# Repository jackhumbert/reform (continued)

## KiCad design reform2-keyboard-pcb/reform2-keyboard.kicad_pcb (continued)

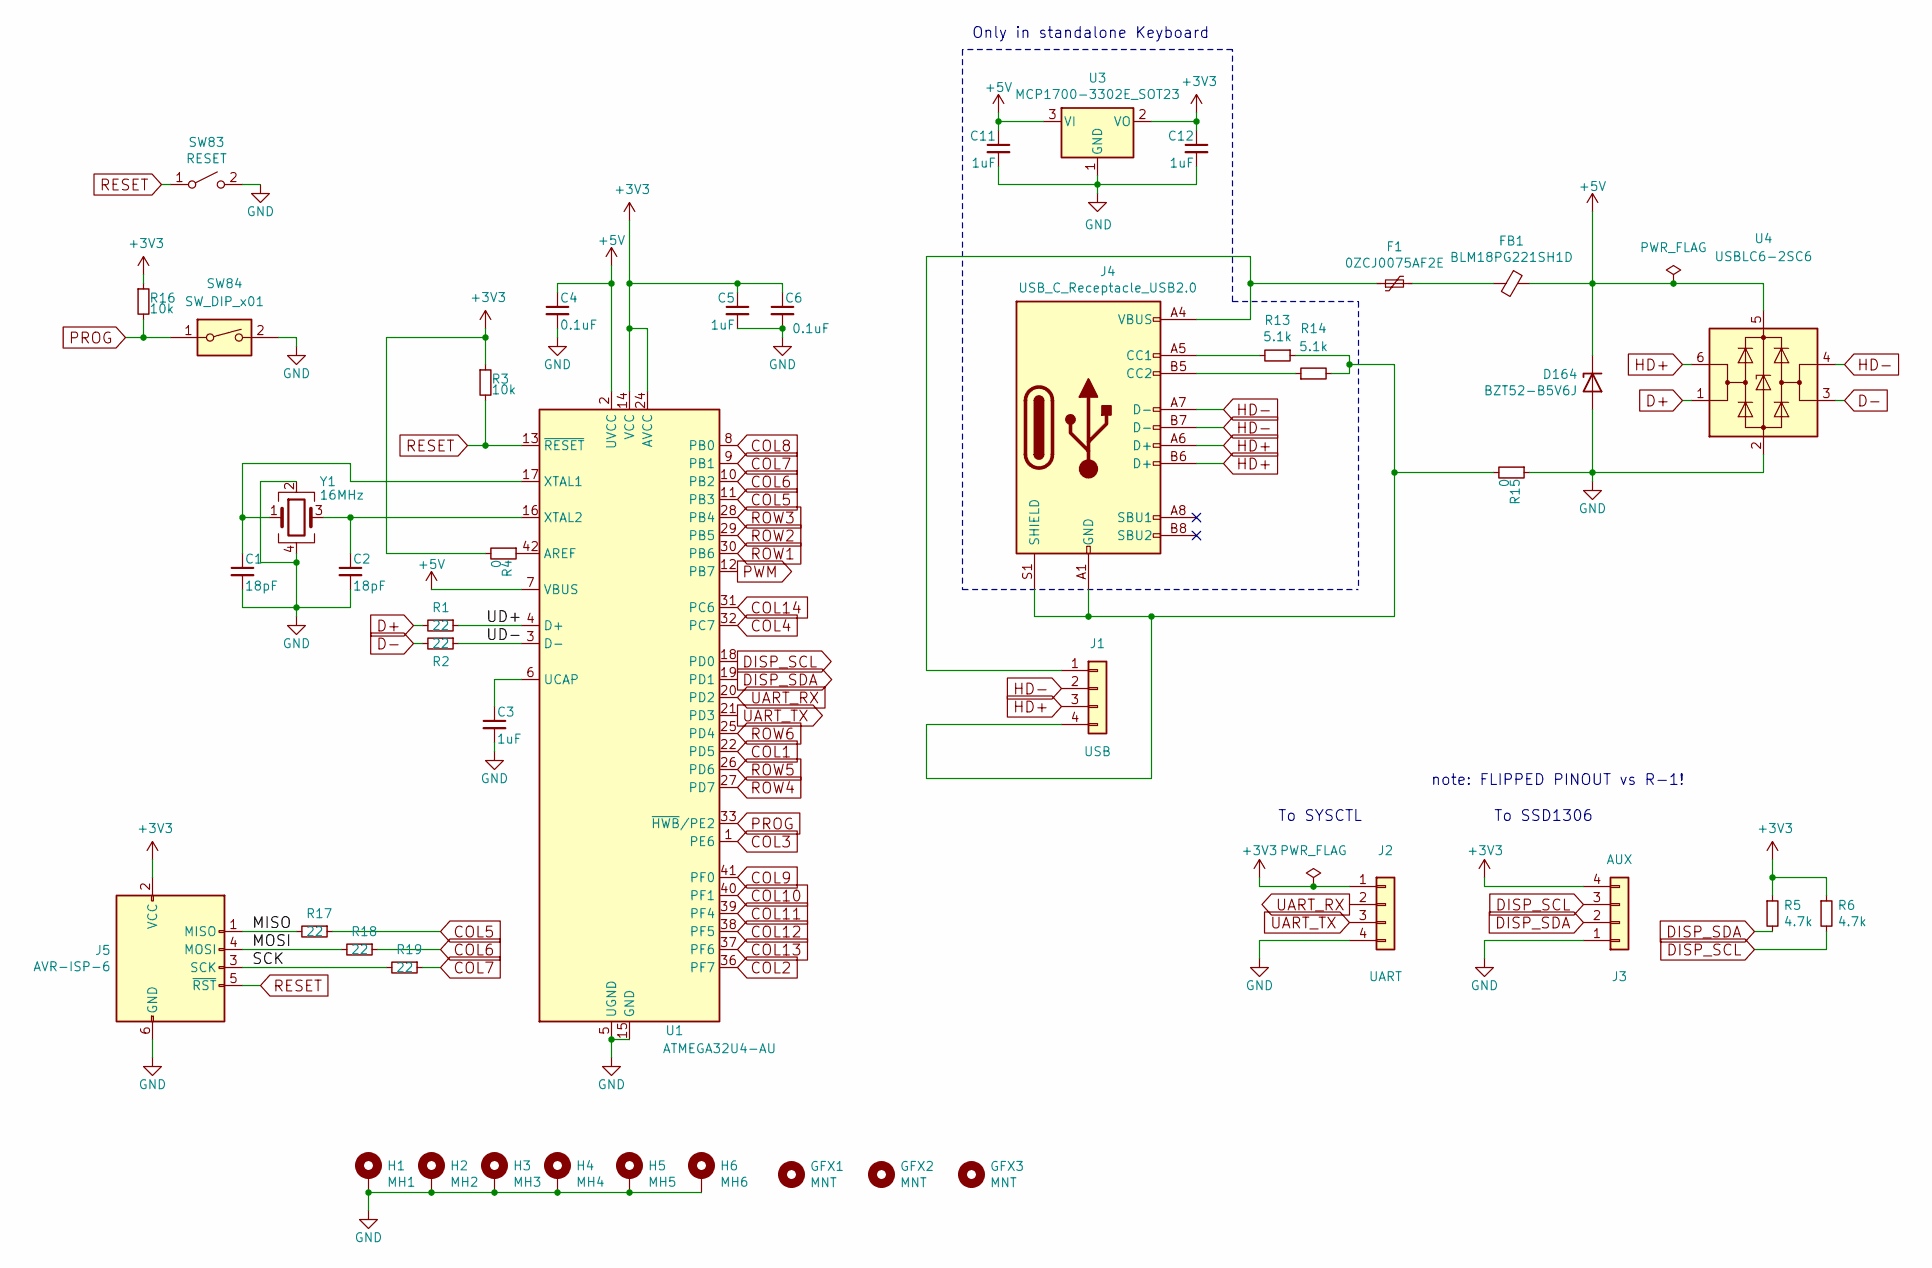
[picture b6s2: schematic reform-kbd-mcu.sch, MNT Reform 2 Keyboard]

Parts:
C1, C2: 18pF; C_0603_1608Metric; LCSC C107040
C3, C5, C11, C12: 1uF; C_0603_1608Metric; LCSC C14664
C4, C6: 0.1uF; C_0603_1608Metric; LCSC C14663
D164: BZT52-B5V6J; D_SOD-123; LCSC C173406
F1: 0ZCJ0075AF2E; R_1206_3216Metric; LCSC C70082
FB1: BLM18PG221SH1D; L_0603_1608Metric; LCSC C14709
GFX1, GFX2: MNT; mntreform
GFX3: MNT; mnt-reform-keyboard-r2-badge
H1: MH1; MountingHole_2.2mm_M2_Pad
H2: MH2; MountingHole_2.2mm_M2_Pad
H3: MH3; MountingHole_2.2mm_M2_Pad
H4: MH4; MountingHole_2.2mm_M2_Pad
H5: MH5; MountingHole_2.2mm_M2_Pad
H6: MH6; MountingHole_2.2mm_M2_Pad
J1: USB; JST_PH_S4B-PH-SM4-TB_1x04-1MP_P2.00mm_Horizontal; LCSC C265332
J2: UART; JST_PH_S4B-PH-SM4-TB_1x04-1MP_P2.00mm_Horizontal; LCSC C265332
J3: AUX; Molex_200528-0040_1x04-1MP_P1.00mm_Horizontal; LCSC C555410
J4: USB_C_Receptacle_USB2.0; USB_C_Receptacle_HRO_TYPE-C-31-M-12; LCSC C165948
J5: AVR-ISP-6; PinHeader_2x03_P2.54mm_Vertical
R1, R2, R17, R18, R19: 22; R_0603_1608Metric; LCSC C107701
R3, R16: 10k; R_0603_1608Metric; LCSC C99198
R4, R15: 0; R_0603_1608Metric; LCSC C95177
R5, R6: 4.7k; R_0603_1608Metric; LCSC C105428
R13, R14: 5.1k; R_0603_1608Metric; LCSC C105580
SW83: RESET; SW_Push_1P1T_NO_CK_KMR2; LCSC C318893
SW84: SW_DIP_x01; SW_DIP_SPSTx01_Slide_Omron_A6S-110x_W8.9mm_P2.54mm; LCSC C402914
U1: ATMEGA32U4-AU; TQFP-44_10x10mm_Pitch0.8mm
U3: MCP1700-3302E_SOT23; SOT-23; LCSC C39051
U4: USBLC6-2SC6; SOT-23-6; LCSC C2687116
Y1: 16MHz; Crystal_SMD_3225-4Pin_3.2x2.5mm; LCSC C70562

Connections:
+3V3: C5.1, C6.1, C12.1, J2.1, J3.4, J5.2 (VCC), R3.1, R4.2, R5.1, R6.1, R16.1, U1.14 (VCC), U1.24 (AVCC), U1.34 (VCC), U1.44 (AVCC), U3.2 (VO)
+5V: C4.1, C11.1, D164.1 (K), FB1.1, U1.2 (UVCC), U1.7 (VBUS), U3.3 (VI), U4.5 (VBUS); also elsewhere on the board
/Reform KBD MCU/MISO: J5.1 (MISO), R17.2
/Reform KBD MCU/MOSI: J5.4 (MOSI), R18.2
/Reform KBD MCU/SCK: J5.3 (SCK), R19.2
/Reform KBD MCU/UD+: R1.1, U1.4 (D+)
/Reform KBD MCU/UD-: R2.1, U1.3 (D-)
COL1: U1.22 (PD5); also elsewhere on the board
COL2: U1.36 (PF7); also elsewhere on the board
COL3: U1.1 (PE6); also elsewhere on the board
COL4: U1.32 (PC7); also elsewhere on the board
COL5: R17.1, U1.11 (PB3); also elsewhere on the board
COL6: R18.1, U1.10 (PB2); also elsewhere on the board
COL7: R19.1, U1.9 (PB1); also elsewhere on the board
COL8: U1.8 (PB0); also elsewhere on the board
COL9: U1.41 (PF0); also elsewhere on the board
COL10: U1.40 (PF1); also elsewhere on the board
COL11: U1.39 (PF4); also elsewhere on the board
COL12: U1.38 (PF5); also elsewhere on the board
COL13: U1.37 (PF6); also elsewhere on the board
COL14: U1.31 (PC6); also elsewhere on the board
D+: R1.2, U4.1 (I/O1)
D-: R2.2, U4.3 (I/O2)
DISP_SCL: J3.3, R6.2, U1.18 (PD0)
DISP_SDA: J3.2, R5.2, U1.19 (PD1)
GND: C1.2, C2.2, C3.2, C4.2, C5.2, C6.2, C11.2, C12.2, D164.2 (A), H1.1, H2.1, H3.1, H4.1, H5.1, H6.1, J2.4, J3.1, J5.6 (GND), R15.1, SW83.2 (B), SW84.2, U1.5 (UGND), U1.15 (GND), U1.23 (GND), U1.35 (GND), U1.43 (GND), U3.1 (GND), U4.2 (GND), Y1.2, Y1.4; also elsewhere on the board
HD+: J1.3, J4.A6 (D+), J4.B6 (D+), U4.6 (I/O1)
HD-: J1.2, J4.A7 (D-), J4.B7 (D-), U4.4 (I/O2)
unnamed: C1.1, U1.17 (XTAL1), Y1.1
unnamed: C2.1, U1.16 (XTAL2), Y1.3
unnamed: C3.1, U1.6 (UCAP)
unnamed: F1.1, J1.1, J4.A4 (VBUS), J4.A9 (VBUS), J4.B4 (VBUS), J4.B9 (VBUS)
unnamed: F1.2, FB1.2
unnamed: J1.4, J4.A1 (GND), J4.A12 (GND), J4.B1 (GND), J4.B12 (GND), J4.S1 (SHIELD), R13.1, R14.2, R15.2
unnamed: J4.A5 (CC1), R13.2
unnamed: J4.B5 (CC2), R14.1
unnamed: R4.1, U1.42 (AREF)
PROG: R16.2, SW84.1, U1.33 (~HWB~/PE2)
PWM: U1.12 (PB7); also elsewhere on the board
RESET: J5.5 (~RST), R3.2, SW83.1 (A), U1.13 (~RESET)
ROW1: U1.30 (PB6); also elsewhere on the board
ROW2: U1.29 (PB5); also elsewhere on the board
ROW3: U1.28 (PB4); also elsewhere on the board
ROW4: U1.27 (PD7); also elsewhere on the board
ROW5: U1.26 (PD6); also elsewhere on the board
ROW6: U1.25 (PD4); also elsewhere on the board
UART_RX: J2.2, U1.20 (PD2)
UART_TX: J2.3, U1.21 (PD3)

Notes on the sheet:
To SSD1306
Only in standalone Keyboard
To SYSCTL
note: FLIPPED PINOUT vs R-1!

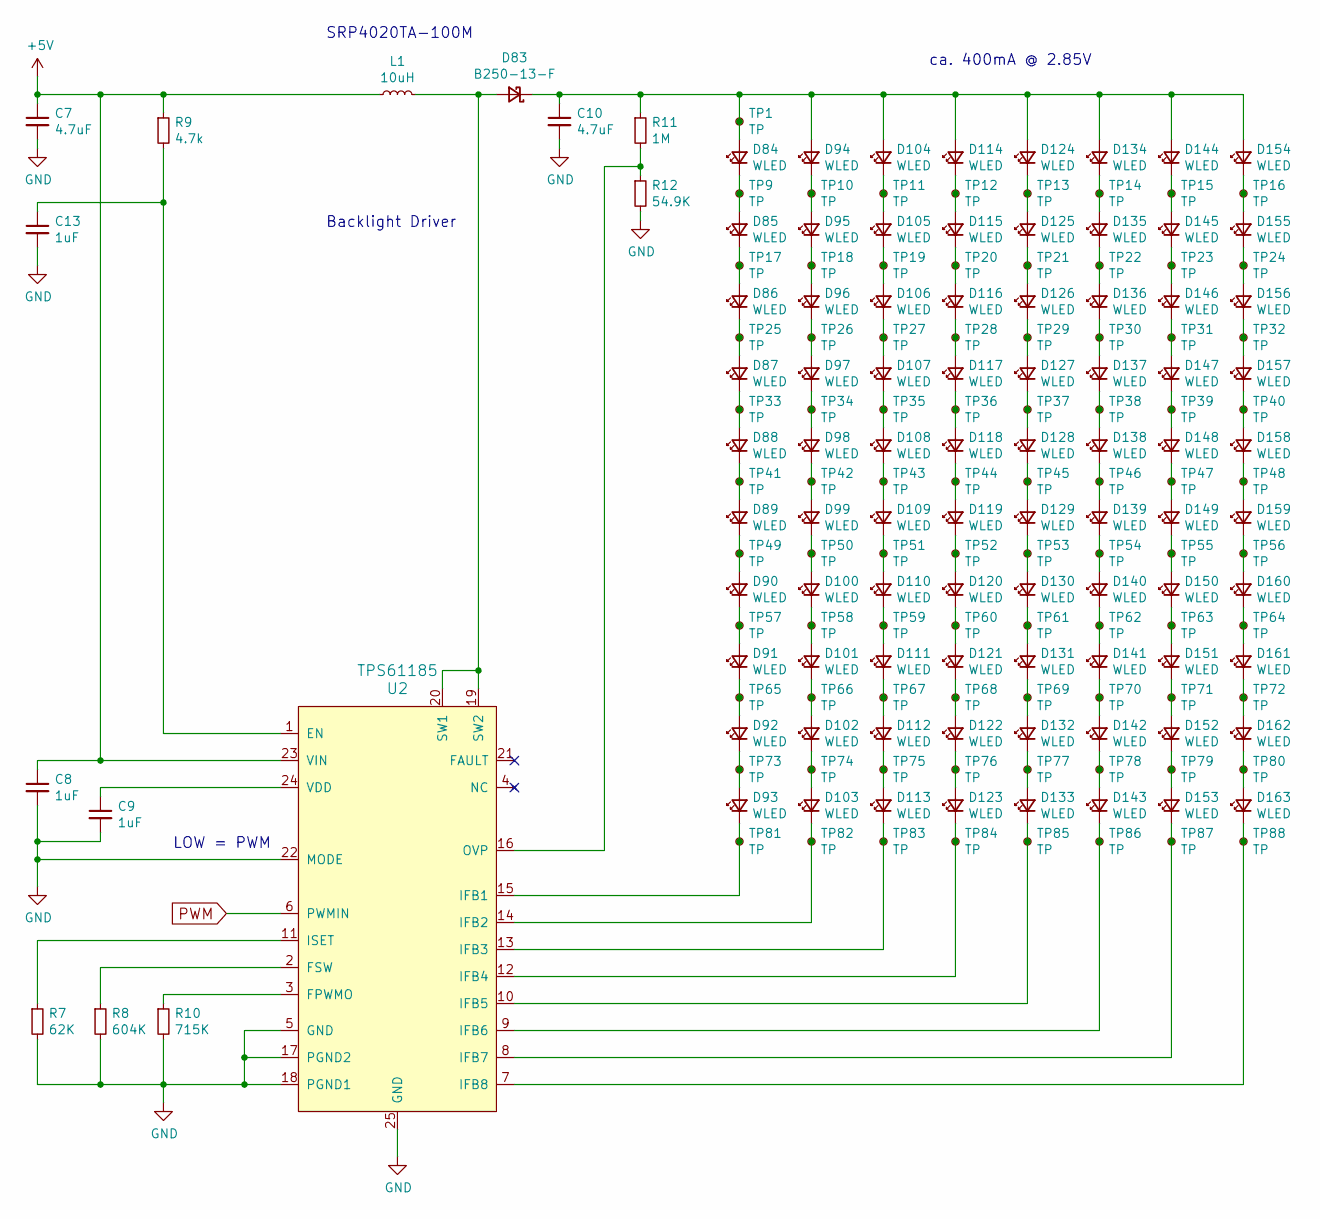
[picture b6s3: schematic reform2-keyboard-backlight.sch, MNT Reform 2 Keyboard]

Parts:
C7, C10: 4.7uF; C_0603_1608Metric; LCSC C90057
C8, C9, C13: 1uF; C_0603_1608Metric; LCSC C14664
D83: B250-13-F; D_SMB_Handsoldering; LCSC C719400
D84, D85, D86, D87, D88, D89, D90, D91, D92, D93, D94, D95, D96, D97, D98, D99, D100, D101, D102, D103, D104, D105, D106, D107, D108, D109, D110, D111, D112, D113, D114, D115, D116, D117, D118, D119, D120, D121, D122, D123, D124, D125, D126, D127, D128, D129, D130, D131, D132, D133, D134, D135, D136, D137, D138, D139, D140, D141, D142, D143, D144, D145, D146, D147, D148, D149, D150, D151, D152, D153, D154, D155, D156, D157, D158, D159, D160, D161, D162, D163: WLED; LED_0603_1608Metric; LCSC C389521
L1: 10uH; IND_SRP4020TA-150M; LCSC C98364
R7: 62K; R_0603_1608Metric; LCSC C137694
R8: 604K; R_0603_1608Metric; LCSC C245986
R9: 4.7k; R_0603_1608Metric; LCSC C105428
R10: 715K; R_0603_1608Metric; LCSC C137685
R11: 1M; R_0603_1608Metric; LCSC C107698
R12: 54.9K; R_0603_1608Metric; LCSC C227961
TP1, TP9, TP10, TP11, TP12, TP13, TP14, TP15, TP16, TP17, TP18, TP19, TP20, TP21, TP22, TP23, TP24, TP25, TP26, TP27, TP28, TP29, TP30, TP31, TP32, TP33, TP34, TP35, TP36, TP37, TP38, TP39, TP40, TP41, TP42, TP43, TP44, TP45, TP46, TP47, TP48, TP49, TP50, TP51, TP52, TP53, TP54, TP55, TP56, TP57, TP58, TP59, TP60, TP61, TP62, TP63, TP64, TP65, TP66, TP67, TP68, TP69, TP70, TP71, TP72, TP73, TP74, TP75, TP76, TP77, TP78, TP79, TP80, TP81, TP82, TP83, TP84, TP85, TP86, TP87, TP88: TP; TestPoint_Pad_1.0x1.0mm
U2: TPS61185; VQFN-24-1EP_4x4mm_P0.5mm_EP2.45x2.45mm; LCSC C2867853

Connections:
+5V: C7.1, C8.1, L1.1, R9.1, U2.23 (VIN); also elsewhere on the board
GND: C7.2, C8.2, C9.2, C10.2, C13.2, R7.2, R8.2, R10.2, R12.2, U2.5 (GND), U2.17 (PGND2), U2.18 (PGND1), U2.22 (MODE), U2.25 (GND); also elsewhere on the board
unnamed: C9.1, U2.24 (VDD)
unnamed: C10.1, D83.1 (K), D84.2 (A), D94.2 (A), D104.2 (A), D114.2 (A), D124.2 (A), D134.2 (A), D144.2 (A), D154.2 (A), R11.1, TP1.1
unnamed: C13.1, R9.2, U2.1 (EN)
unnamed: D83.2 (A), L1.2, U2.19 (SW2), U2.20 (SW1)
unnamed: D84.1 (K), D85.2 (A), TP9.1
unnamed: D85.1 (K), D86.2 (A), TP17.1
unnamed: D86.1 (K), D87.2 (A), TP25.1
unnamed: D87.1 (K), D88.2 (A), TP33.1
unnamed: D88.1 (K), D89.2 (A), TP41.1
unnamed: D89.1 (K), D90.2 (A), TP49.1
unnamed: D90.1 (K), D91.2 (A), TP57.1
unnamed: D91.1 (K), D92.2 (A), TP65.1
unnamed: D92.1 (K), D93.2 (A), TP73.1
unnamed: D93.1 (K), TP81.1, U2.15 (IFB1)
unnamed: D94.1 (K), D95.2 (A), TP10.1
unnamed: D95.1 (K), D96.2 (A), TP18.1
unnamed: D96.1 (K), D97.2 (A), TP26.1
unnamed: D97.1 (K), D98.2 (A), TP34.1
unnamed: D98.1 (K), D99.2 (A), TP42.1
unnamed: D100.1 (K), D101.2 (A), TP58.1
unnamed: D99.1 (K), D100.2 (A), TP50.1
unnamed: D101.1 (K), D102.2 (A), TP66.1
unnamed: D102.1 (K), D103.2 (A), TP74.1
unnamed: D103.1 (K), TP82.1, U2.14 (IFB2)
unnamed: D104.1 (K), D105.2 (A), TP11.1
unnamed: D105.1 (K), D106.2 (A), TP19.1
unnamed: D106.1 (K), D107.2 (A), TP27.1
unnamed: D107.1 (K), D108.2 (A), TP35.1
unnamed: D108.1 (K), D109.2 (A), TP43.1
unnamed: D109.1 (K), D110.2 (A), TP51.1
unnamed: D110.1 (K), D111.2 (A), TP59.1
unnamed: D111.1 (K), D112.2 (A), TP67.1
unnamed: D112.1 (K), D113.2 (A), TP75.1
unnamed: D113.1 (K), TP83.1, U2.13 (IFB3)
unnamed: D114.1 (K), D115.2 (A), TP12.1
unnamed: D115.1 (K), D116.2 (A), TP20.1
unnamed: D116.1 (K), D117.2 (A), TP28.1
unnamed: D117.1 (K), D118.2 (A), TP36.1
unnamed: D118.1 (K), D119.2 (A), TP44.1
unnamed: D119.1 (K), D120.2 (A), TP52.1
unnamed: D120.1 (K), D121.2 (A), TP60.1
unnamed: D121.1 (K), D122.2 (A), TP68.1
unnamed: D122.1 (K), D123.2 (A), TP76.1
unnamed: D123.1 (K), TP84.1, U2.12 (IFB4)
unnamed: D124.1 (K), D125.2 (A), TP13.1
unnamed: D125.1 (K), D126.2 (A), TP21.1
unnamed: D126.1 (K), D127.2 (A), TP29.1
unnamed: D127.1 (K), D128.2 (A), TP37.1
unnamed: D128.1 (K), D129.2 (A), TP45.1
unnamed: D129.1 (K), D130.2 (A), TP53.1
unnamed: D130.1 (K), D131.2 (A), TP61.1
unnamed: D131.1 (K), D132.2 (A), TP69.1
unnamed: D132.1 (K), D133.2 (A), TP77.1
unnamed: D133.1 (K), TP85.1, U2.10 (IFB5)
unnamed: D134.1 (K), D135.2 (A), TP14.1
unnamed: D135.1 (K), D136.2 (A), TP22.1
unnamed: D136.1 (K), D137.2 (A), TP30.1
unnamed: D137.1 (K), D138.2 (A), TP38.1
unnamed: D138.1 (K), D139.2 (A), TP46.1
unnamed: D139.1 (K), D140.2 (A), TP54.1
unnamed: D140.1 (K), D141.2 (A), TP62.1
unnamed: D141.1 (K), D142.2 (A), TP70.1
unnamed: D142.1 (K), D143.2 (A), TP78.1
unnamed: D143.1 (K), TP86.1, U2.9 (IFB6)
unnamed: D144.1 (K), D145.2 (A), TP15.1
unnamed: D145.1 (K), D146.2 (A), TP23.1
unnamed: D146.1 (K), D147.2 (A), TP31.1
unnamed: D147.1 (K), D148.2 (A), TP39.1
unnamed: D148.1 (K), D149.2 (A), TP47.1
unnamed: D149.1 (K), D150.2 (A), TP55.1
unnamed: D150.1 (K), D151.2 (A), TP63.1
unnamed: D151.1 (K), D152.2 (A), TP71.1
unnamed: D152.1 (K), D153.2 (A), TP79.1
unnamed: D153.1 (K), TP87.1, U2.8 (IFB7)
unnamed: D154.1 (K), D155.2 (A), TP16.1
unnamed: D155.1 (K), D156.2 (A), TP24.1
unnamed: D156.1 (K), D157.2 (A), TP32.1
unnamed: D157.1 (K), D158.2 (A), TP40.1
unnamed: D158.1 (K), D159.2 (A), TP48.1
unnamed: D159.1 (K), D160.2 (A), TP56.1
unnamed: D160.1 (K), D161.2 (A), TP64.1
unnamed: D161.1 (K), D162.2 (A), TP72.1
unnamed: D162.1 (K), D163.2 (A), TP80.1
unnamed: D163.1 (K), TP88.1, U2.7 (IFB8)
unnamed: R7.1, U2.11 (ISET)
unnamed: R8.1, U2.2 (FSW)
unnamed: R10.1, U2.3 (FPWMO)
unnamed: R11.2, R12.1, U2.16 (OVP)
PWM: U2.6 (PWMIN); also elsewhere on the board

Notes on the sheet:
LOW = PWM
SRP4020TA-100M
ca. 400mA @ 2.85V
Backlight Driver

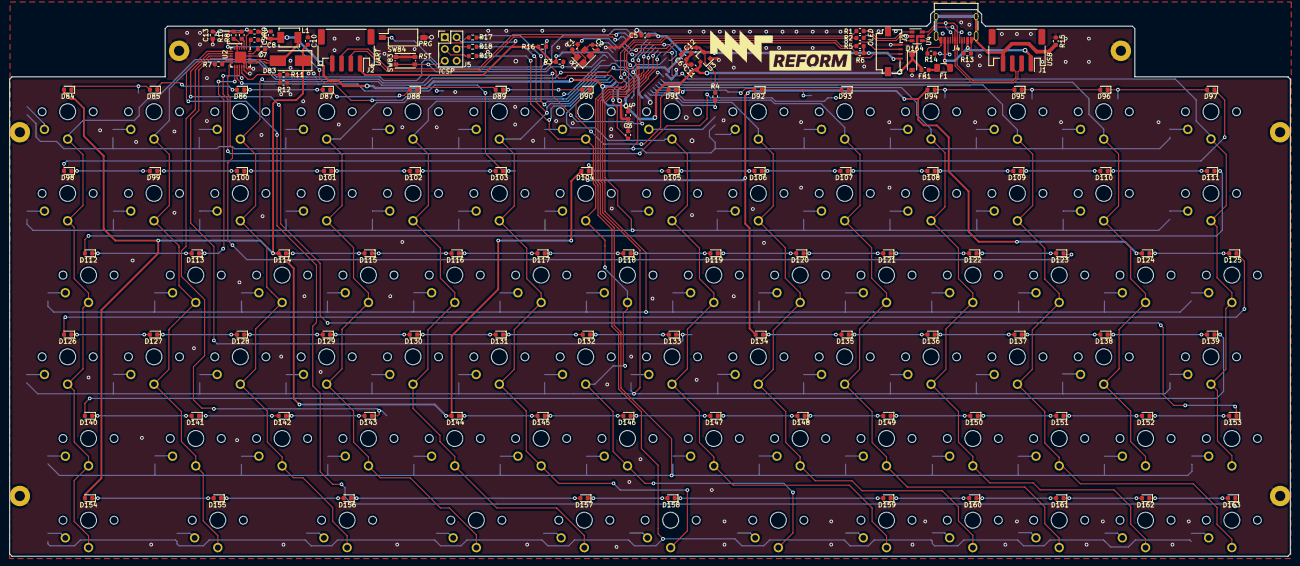
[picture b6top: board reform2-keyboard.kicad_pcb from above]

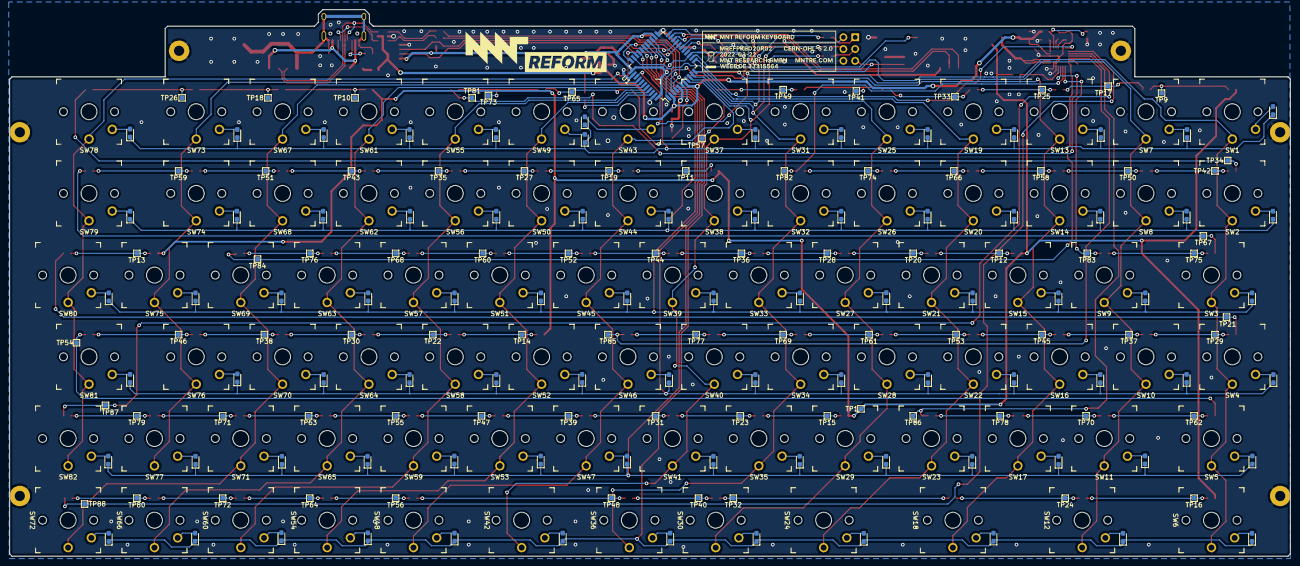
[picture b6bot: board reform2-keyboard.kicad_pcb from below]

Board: 2 copper layers, 275.9 x 117.8 mm, 383 parts (166 on the bottom side), 218 nets.

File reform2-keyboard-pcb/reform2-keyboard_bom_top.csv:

"Comment","Designator","Footprint","LCSC Part #"
"Choc","SW1 SW7 SW13 SW19 SW25 SW31 SW37 SW43 SW49 SW55 SW61 SW67 SW73 SW78 SW8 SW14 SW20 SW26 SW32 SW38 SW44 SW50 SW56 SW62 SW68 SW74 SW79 SW9 SW15 SW21 SW27 SW33 SW39 SW45 SW51 SW57 SW63 SW69 SW75 SW80 SW4 SW10 SW16 SW22 SW28 SW34 SW40 SW46 SW52 SW58 SW64 SW70 SW76 SW81 SW5 SW11 SW17 SW23 SW29 SW35 SW41 SW47 SW53 SW59 SW65 SW71 SW77 SW82 SW6 SW12 SW18 SW24 SW30 SW36 SW42 SW3 SW2 SW48 SW54 SW60 SW66 SW72","","C400230"
"MMDL914T1G","D1 D7 D13 D19 D25 D31 D37 D43 D49 D55 D61 D67 D73 D78 D8 D14 D20 D26 D32 D38 D44 D50 D56 D62 D68 D74 D79 D9 D15 D21 D27 D33 D39 D45 D51 D57 D63 D69 D75 D80 D4 D10 D16 D22 D28 D34 D40 D46 D52 D58 D64 D70 D76 D81 D5 D11 D17 D23 D29 D35 D41 D47 D53 D59 D65 D71 D77 D82 D6 D12 D18 D24 D30 D36 D42 D3 D2 D48 D54 D60 D66 D72","","C193404"
"18pF","C1 C2","","C107040"
"1uF","C3 C5 C11 C12 C9 C8 C13","","C14664"
"22","R2 R1 R17 R18 R19","","C107701"
"0.1uF","C4 C6","","C14663"
"10k","R3 R16","","C99198"
"16MHz","Y1","","C70562"
"RESET","SW83","","C318893"
"SW_DIP_x01","SW84","","C402914"
"0","R4 R15","","C95177"
"UART","J2","","C265332"
"AUX","J3","","C555410"
"4.7k","R5 R6 R9","","C105428"
"USB_C_Receptacle_USB2.0","J4","","C165948"
"5.1k","R13 R14","","C105580"
"MCP1700-3302E_SOT23","U3","","C39051"
"USBLC6-2SC6","U4","","C2687116"
"USB","J1","","C265332"
"0ZCJ0075AF2E","F1","","C70082"
"BLM18PG221SH1D","FB1","","C14709"
"BZT52-B5V6J","D164","","C173406"
"AVR-ISP-6","J5","",""
"TPS61185","U2","","C2867853"
"1M","R11","","C107698"
"4.7uF","C10 C7","","C90057"
"54.9K","R12","","C227961"
"715K","R10","","C137685"
"604K","R8","","C245986"
"62K","R7","","C137694"
"B250-13-F","D83","","C2758510"
"WLED","D84 D85 D86 D87 D88 D89 D90 D91 D94 D95 D96 D97 D98 D99 D100 D101 D104 D105 D106 D107 D108 D109 D110 D111 D114 D115 D116 D117 D118 D119 D120 D121 D124 D125 D126 D127 D128 D129 D130 D131 D134 D135 D136 D137 D138 D139 D140 D141 D144 D145 D146 D147 D148 D149 D150 D151 D154 D155 D156 D157 D158 D159 D160 D161 D92 D93 D102 D103 D112 D113 D122 D123 D132 D133 D142 D143 D152 D153 D162 D163","","C389521"
"10uH","L1","","C98364"

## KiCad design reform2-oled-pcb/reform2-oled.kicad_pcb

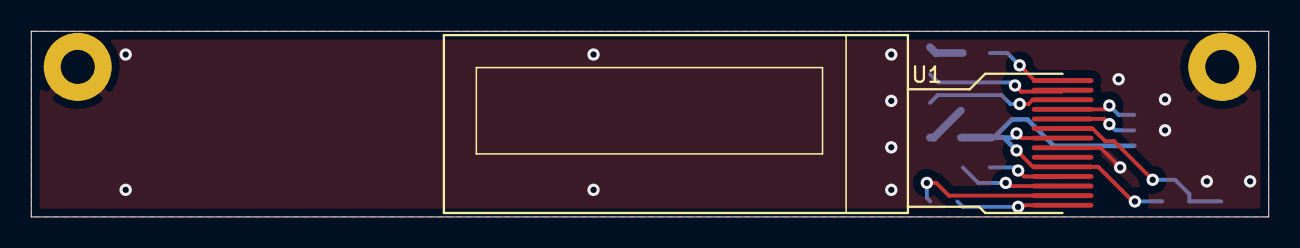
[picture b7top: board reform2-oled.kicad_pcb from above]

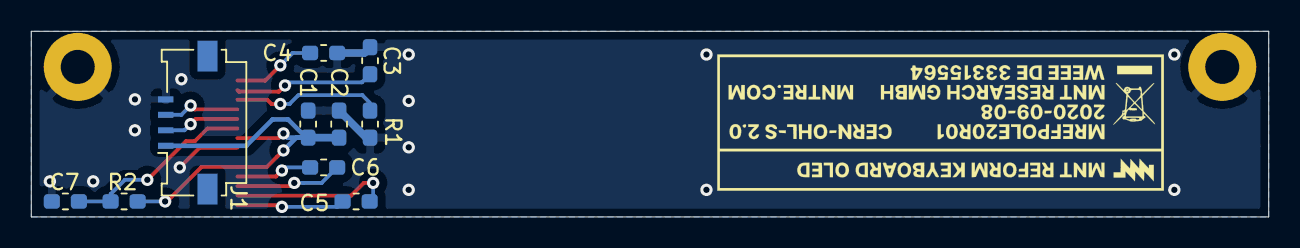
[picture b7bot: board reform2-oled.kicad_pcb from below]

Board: 2 copper layers, 80.0 x 12.0 mm, 14 parts (11 on the bottom side), 12 nets.

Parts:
C1, C2, C5, C6, C7: 1uF; C_0603_1608Metric_Pad1.05x0.95mm_HandSolder
C3, C4: 10uF; C_0603_1608Metric_Pad1.05x0.95mm_HandSolder
GFX2: BADGE; reform2-oled-badge
H1: MH1; MountingHole_2.2mm_M2_Pad
H2: MH2; MountingHole_2.2mm_M2_Pad
J1: AUX; Molex_200528-0040_1x04-1MP_P1.00mm_Horizontal
R1: 330k; R_0603_1608Metric_Pad1.05x0.95mm_HandSolder
R2: 4.7k; R_0603_1608Metric_Pad1.05x0.95mm_HandSolder
U1: SSD1306; SSD1306_OLED-0.91-128x32

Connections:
+3V3: C1.1, C2.1, J1.1, R2.2, U1.5, U1.8
DISP_SCL: J1.2, U1.10
DISP_SDA: J1.3, U1.11
GND: C1.2, C2.2, C3.2, C4.2, C7.2, H1.1, H2.1, J1.4, R1.2, U1.7
unnamed: C3.1, U1.13
unnamed: C4.1, U1.14
unnamed: C5.1, U1.1
unnamed: C5.2, U1.2
unnamed: C6.1, U1.3
unnamed: C6.2, U1.4
unnamed: C7.1, R2.1, U1.9
unnamed: R1.1, U1.12

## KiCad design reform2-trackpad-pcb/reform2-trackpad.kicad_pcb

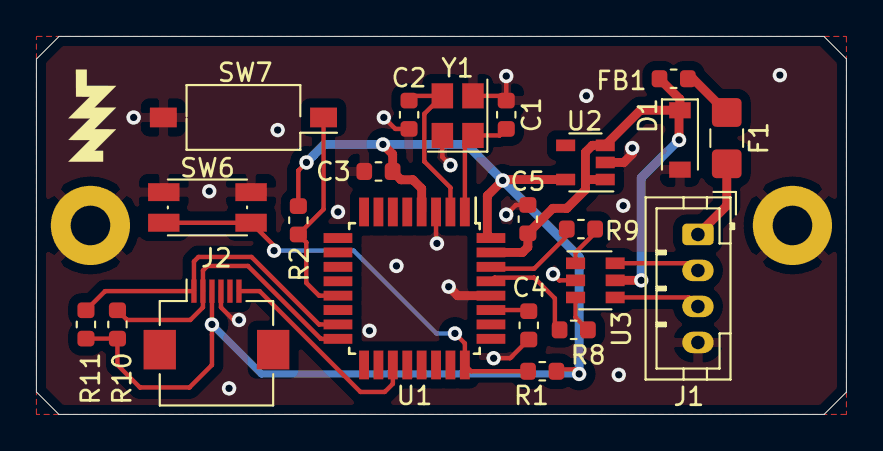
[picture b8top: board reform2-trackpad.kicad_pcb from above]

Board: 2 copper layers, 45.0 x 21.0 mm, 26 parts (1 on the bottom side), 19 nets.

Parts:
C1, C2: 18pF; C_0603_1608Metric
C3, C5: 0.1uF; C_0603_1608Metric
C4: 1uF; C_0603_1608Metric
D1: BZT52-B5V6J; D_SOD-123
F1: 0ZCJ0075AF2E; Fuse_1206_3216Metric_Castellated
FB1: BLM18PG221SH1D; L_0603_1608Metric
J1: Conn_USB; JST_PH_B4B-PH-K_1x04_P2.00mm_Vertical
J2: Conn_01x06_Female; Hirose_FH12-6S-0.5SH_1x06-1MP_P0.50mm_Horizontal
MK1: BADGE; reform2-trackpadctrl-badge
MK5, MK6: Mounting_Hole; MountingHole_2.2mm_M2_Pad
MK13: LOGO; mnt-minilogo
R1, R2: 10k; R_0603_1608Metric
R8, R9: 22; R_0603_1608Metric
R10, R11: 4.7k; R_0603_1608Metric
SW6: SW_RST; Diptronics-PTLP2
SW7: SW_HWB; SW_DIP_SPSTx01_Slide_Omron_A6S-110x_W8.9mm_P2.54mm
U1: ATmega32U2-AU; TQFP-32_7x7mm_P0.8mm
U2: TLV75533PDBV; SOT-23-5
U3: USBLC6-2SC6; SOT-23-6
Y1: Crystal_GND24; Crystal_SMD_3225-4Pin_3.2x2.5mm

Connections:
+3V3: C3.1, J2.3, R1.1, R2.2, R10.2, R11.2, U1.4, U1.32, U2.5
+5V: C5.1, D1.1, FB1.1, U1.31, U2.1, U2.3, U3.5
/5V_IN: F1.2, J1.1
/PD+: J1.3, U3.4
/PD-: J1.2, U3.6
/UD+: R8.1, U3.3
/UD-: R9.2, U3.1
GND: C1.2, C2.1, C3.2, C4.2, C5.2, D1.2, J1.4, J2.4, MK5.1, MK6.1, SW6.1, SW7.2, U1.3, U1.28, U2.2, U3.2, Y1.2, Y1.4
unnamed: C1.1, U1.1, Y1.1
unnamed: C2.2, U1.2, Y1.3
unnamed: C4.1, U1.27
unnamed: F1.1, FB1.2
unnamed: R1.2, SW6.2, U1.24
unnamed: R2.1, SW7.1, U1.13
unnamed: R8.2, U1.29
unnamed: R9.1, U1.30
RDY: J2.6, U1.19
SCL: J2.2, R10.1, U1.16
SDA: J2.1, R11.1, U1.15

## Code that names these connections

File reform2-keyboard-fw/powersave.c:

/*
  MNT Reform 2.0 Keyboard Firmware
  See keyboard.c for Copyright
  SPDX-License-Identifier: MIT
*/

#include <avr/io.h>
#include <avr/sleep.h>
#include "powersave.h"
#include "keyboard.h"
#include "oled.h"

/* Setup the AVR to enter the Power-Down state to greatly save power.
 * Configures all outputs to be in the low state if possible, and disables
 * services like USB and Serial.
 *
 * Will leave the ports setup so that the Circle key row is being scanned
 * so when the watchdog wakes up it can quickly check and go back to sleep if not
 * Added by Chartreuse - 2021/08/14
 *
 */
void keyboard_power_off(void)
{
  USB_Disable(); // Stop USB stack so it doesn't wake us up

  // turn off backlight, but don't overwrite setting
  OCR0A = 0;

  // Turn off OLED to save power
  gfx_clear_screen();
  gfx_off();
  // Disable ADC to save even more power
  ADCSRA=0;

  cli();    // No interrupts

  // Set all ports not floating if possible, leaving pullups alone
  PORTB=0x3F; // Leave pull-up on all the columns on PB0-3, drive rows 2-3 high, 1-low
  PORTC=0xC0;
  PORTD=0xF0; // Keep pullup on PD5 like setup did, drive rows 4,5,6 high
  PORTE=0x40; // Pullup on PE6
  PORTF=0xFF; // Pullups on PF (columns)
  // ROW1 is the only row driven low and left low, thus is always ready to be read out
  // We just need to check COL14 (PC6) if it is low (pressed) or high

  // Unfortunately the circle key is on COL14(PC6) which doesn't have pin change interrupt
  // capabilities, so we need to wake up every so often to check if it is pressed, and
  // if so bring us out of power-off
  // We can use the Watchdog timer to do this.

  do {
    // Setting WDT parameters must be done within 4 cycles of setting WDCE, so interrupts
    // must be disabled.
    cli();

    wdt_reset();

    // Enable writes to watchdog, then set interrupt-only mode, 1s timeout.
    // (Interrupt-only mode is preferred to interrupt-and-reset mode, because
    // the latter has the risk of WDT-induced bootloops if the bootloader doesn't
    // correctly handle WDT resets. Whereas we have a physical reset button, if
    // a hard reset is actually needed.)
    WDTCSR = (1<<WDCE) | (1<<WDE);
    WDTCSR = (1<<WDIE) | (0<<WDE) | (0<<WDP3) | (1<<WDP2) | (1<<WDP1) | (0<<WDP0);

    // Enter Power-save mode
    set_sleep_mode(SLEEP_MODE_PWR_DOWN);
    sleep_enable();
    sei();              // Enable interrupts so we can actually wake
    sleep_cpu();        // Actually go to sleep
    // Zzzzzz
    sleep_disable();    // We've woken up
    wdt_disable();      // Disable watchdog for now
    sei();
    // Check if circle key has been pressed (active-low)
    // If not reset the watchdog and try again
  } while(PINC&(1<<6));

  // Resume and reinitialize hardware
  setup_hardware();
}

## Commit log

2020-11-17 reform2-lpc-fw: add shell.nix
    Nix users can enter a shell with the appropriate toolchain by issuing the
    `nix-shell` command in the reform2-lpc-fw directory.
2020-12-27 try to determine charge state based on current, not only voltage
2020-12-27 wip: add more debug to cell status
2021-01-07 WIP OLED menu system
2021-01-13 refactor circle key handling
2021-01-13 shuffle cell info format around
2021-01-13 WIP extract new cell info format from LPC
2021-01-13 lpc: clean up cell status command to include gauge
2021-01-13 keyboard: clean up cell status / fuel gauge frontend
2021-01-20 WIP: keyboard: remove unused bat_volts
2021-01-20 lpc-fw: remove unhelpful powerdown
2021-02-03 debounce revamp
2021-02-04 experiment: auxpwr toggle
2021-02-17 keyboard: commands for som wake, and allow some LPC commands via HID
2021-02-17 keyboard: remove aux pwr from menu, add wake option
2021-02-17 keyboard: OLED formatting tweaks
2021-02-18 lpc-fw: commands for uart imx report toggle and wake; include FW rev date in status
2021-02-18 keyboard-fw: rename gfx functions; add HID invert row command; finalize status screen; replace hyper with rgui modifier
2021-02-18 keyboard-fw: tweak status display
2021-02-18 keyboard-fw: display tweak, leave logo on
2021-02-18 trackball-fw: don't light up on wheel mode; make LEDs addressable via HID
2021-02-18 keyboard-fw: make backlight controllable via HID
2021-02-18 WIP qwerty v4
2021-03-02 reform2-handbook: remove obsolete TODO.md
2021-03-02 keyboard: don't reenter menu mode until all keys have been lifted again
2021-03-02 keyboard: prototype low batt polling and alert
2021-03-02 keyboard: bump rev
2021-03-05 fix status labels, bump release
2021-03-09 kbd/lpc: fix alignment of amps/battery gauge
2021-03-09 lpc: fix mA sign type
2021-03-09 kbd/lpc: fix and document gauge alignment
2021-03-11 keyboard: add standalone option
2021-03-15 add keyboard lettering v5: qwerty-us and qwertz-de
2021-03-15 keyboard-fw 20210315
2021-03-15 keyboard-fw: fixes for non-standalone version
2021-03-16 trackpad-fw: nicer, smoother, better
2021-04-13 motherboard: add the split-up and cleaned up schematics that were made for the book
2021-04-19 reform2-lpc: fix battery percentage; fix overvoltage for fixed R2 board; more status info
2021-04-19 reform2-keyboard-fw: fix battery gauge offset
2021-04-19 reform2-lpc-fw: different end-of-charge recognition currents for r2/r3
2021-05-31 keyboard: add neo2 version
2021-05-31 keyboard: default to non-standalone
2021-06-10 add reform2 case sources in fusion format
2021-06-10 reform2: update PCBs incl. badges to production revs, add keyboard lettering, misc docs
2021-07-14 trackball: don't send left click on left wheel button
2021-07-25 add horizontal wheel (pan) and hi res scrolling
2021-07-25 trackball: tweak wheel sensitivity
2021-07-25 trackpad: implement horizontal and hi-res scroll/pan
2021-07-30 trackpad: add glass/glue/gasket assembly STEP
2021-07-30 add speakers and serial cables spec
2021-07-30 add full assembly instructions
2021-07-30 assembly: add motherboard, battery pack pcba references
2021-07-30 assembly: reduce image size
2021-07-30 add csv BOMs
2021-07-30 assembly: add CNC parts sources and fix some references
2021-08-16 Initial Watchdog Based Power-off test
2021-08-16 Working power-down test, with screen off
2021-08-16 Power down ADC to save even more power.
2021-08-16 Renamed power-down menu item
2021-08-16 Enabled keyboard power-off when system turned off
2021-09-06 LPC: when not charging, regularly go to deep sleep for 1 second
2021-09-06 keyboard: add constant for COLS, add magic number for layout editor
2021-09-07 Fixed WDT timeout to actually be 1s (instead of 2s)
2021-09-24 experiment: try to wakeup lpc on timeout
2021-09-24 kbd: LPC wakeup routine and wrapper for commands with retry; power off kbd on shutdown via main CPU
2021-09-24 lpc: sleep in 3 states; next_state; missing cells only between 1 to 7 cells; force sleep mode for testing
2021-09-24 lpc: don't sleep if som is powered
2021-09-24 kbd: bump revision
2021-09-24 kbd: increase battery alert check interval
2021-09-25 lpc: report som power state; 15 mins powersave holdoff time
2021-09-27 kbd: parse and react to remote system power state in poll; poll less often
2021-09-27 kbd: show som on/off state; formatting tweaks; wake directly to menu; sleep 1s instead of 2s
2021-09-27 kbd: hide kbd power-off menu item
2021-09-27 kbd: don't overwrite brightness setting in sleep
2021-09-29 lpc: don't sleep in cell missing state
2021-09-29 lpc: flash.sh: add comment
2021-10-01 lpc: add cooldown state, try not to overheat discharge resistors when balancing
2021-11-21 keyboard: bitmap command wip
2021-11-21 keyboard: html layout editor sketch
2021-11-21 keyboard: WIP some temp. example code for various hacky things
2021-12-05 mac layout remap & fn layering functionality
2021-12-12 Refactoring that splits Keyboard.c into a bunch of modules
2021-12-13 kbd: default matrix: add missing row 6
2021-12-13 kbd: implement media controller device; move matrix to .h files to make make happy
2021-12-22 kbd: remote: don't try remote commands if we're standalone
2022-01-04 keyboard: add OLED graphics demo
2022-01-09 kbd: matrix.h: remove FIXME
2022-01-09 keyboard: kbdgfx: ability to load bitmap, example scripts
2022-01-09 keyboard: standalone: jump to bootloader option
2022-01-31 add mnt based/remix symbols for derived works
2022-02-21 keyboard-fw: adopt Vs name; default to laptop version
2022-02-27 trackball: init usb first, reduce delays; untabify
2022-02-27 case ports: add fc and step files for metal version
2022-02-27 batterypack: add upstream pack sources
2022-03-18 keyboard: add pcb version that has almost all components on the front side, with parts from lcsc
2022-05-17 keyboard-fw: don't disable WDT during its interrupt handler
2022-05-17 keyboard-fw: interrupts must be disabled while WDT parameters are set
2022-05-17 keyboard-fw: use interrupt-only WDT mode, not interrupt-and-reset
2022-06-12 lpc+kbd: Disable circle+1 power on cmd when SoM is already on
    I encountered this a few too many times when messing around with the
    menu. Previously, this would power-cycle the machine, which seems like
    an undesirable behaviour.
2022-06-20 add spi handler to firmware
2022-06-20 minimal driver code
2022-06-21 cleanup some fw code
2022-06-21 fix encoding errors for lpc commands
2022-06-21 fix driver names, add support for power supply class
2022-06-21 give it a bettery battery name
2022-06-22 add type field
2022-06-22 cleanup and fixes
2022-06-23 remove constant logging for perf and uart congestion reasons, switch to O2
2022-06-24 replace delay with sleep per kernel doc recomendations
2022-07-21 keyboard: add WIP R-2D version, atmega RC notes
2022-08-22 trackball pcb: add v2 with rp2040 mcu
2022-08-30 bb2.1 snapshot
2022-09-01 protected battery pack: add release candidate
2022-09-01 keyboard-fw: fix 'display' definition
2022-09-01 keyboard-fw: mechanism for menu page auto-refresh; auto-refresh battery status every 2 seconds
2022-09-06 imx8mplus adapter initial checkin
2022-10-05 keyboard-fw: fix wrong command for OLED clearing
2022-10-05 reform2-lpc-fw: allow faster clock on SPI0
2022-10-05 reform2-lpc-fw: simplify SPI0 response logic
2022-10-05 trackball: dont force send report
    The HID library takes care of comparing with the
    previous report sent, avoiding lots of redundant
    report processing on the host.
2022-10-05 keyboard-fw: fix non-functional Delete key on QWERTY US variant if Hyper is pressed or mode enabled
2022-10-05 keyboard-fw: bind Hyper+F1/F2 to display brightness decrement/increment
2022-10-05 keyboard-fw: simplify get_media_keys
2022-10-05 keyboard-fw: remove unused media control report bits
2022-10-06 keyboard-fw: use the right scancodes for prev/next track to avoid possible confusion
2022-10-06 keyboard-fw: fix the ordering of media keys
2022-10-06 imx8mplus: first rev routed
2022-10-07 imx8mplus: moved some things around; final tweaks and export for first test order
2022-10-07 imx8mplus: last minute diff pair length tuning
2022-10-14 WIP motherboard 2.5 checkpoint
2022-10-15 kbd fw: lpc wakeup clear serial, delay after write, treat '\0' as normal response from LPC
2022-10-26 mb25-pcb: routing snapshot (0 unrouted)
2022-10-27 motherboard 2.5 snapshot: fully routed and cleaned up
2022-11-01 motherboard25: r-1 snapshot, ordered for test bringup
2022-11-01 add initial reform2-keyboard-lettering visicut files
2022-11-01 keyboard-lettering: add v6 qwertz
2022-11-08 imx8mplus: correct the mezzanine footprint, reroute everything, d-2 off to fab
2022-11-09 imx8mplus: change drill size to 0.2mm, add optional 3v3 source via reset pin
2023-01-17 reform2-keyboard3 initial design
2023-01-17 reform2-keyboard3: bump date, revision
2023-02-02 reform2-trackball2-fw: add RP2040 version of trackball firmware
2023-04-14 only talk to uart lines when needed
